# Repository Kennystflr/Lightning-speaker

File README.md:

# Lightning-speaker
Project of Kenny Saint Fleur, Mathys Minsac, Lavallee Alexandre, Florian Bonnet--Galand and Victor Morel. 1st Year ENSEA students.
Design of the electronic board for a speaker.
Using a STM32 microcontroller, audio codec and two class D amplifiers.

The purpose of this project is to design the electronic of a speaker. More specifically the goal is to take an entry signal from Jack 6.35 mm connector and to have sound coming out of a stereo loudspeaker. 
We could also have a parametric eq using 2 encoders 1 for the gain and 1 for the frequency we would be changing.
We also want to have the system working on battery with Usb-C power delivery to charge-up the battery and power up the system even if there is no battery connected.

There is a schematic of the projects detailed review on this repository's root. 

Basically, we would be calcultating coeficients for the SGTL5000 audio codec with the STM32 from the encoder's command. We can command up to 4 different filters with this method.
Then we would apply filters to the audio codec by sending the filter's coeficients through I2C communication protocol to the SGTL5000.
About the signal itself, it would enter into the audio codec, pass through the filters, be transmitted to the STM32 using I2S communication protocol and then would go through the Half Bridge Class D audio amplifer.
To charge up the battery, the 9V power supply (negociated with a source by the STM32) goes through a BMS who can bypass the battery in case it is dead or missing.

An issue we have met doing this was that the Half bridge was commuting between a positive voltage and ground which was a bad for the loudspeakears as the load. To resolve that we had to cut the rms continuous voltage 
using a genuinely calculated capacity.

As IC references we have :
-Microprocessor : STM32G491CET6
-Audio codec :SGTL5000XNLA3
-Battery Management System : BQ25306RTET
- USB-C protection IC : TCPP01-M12
- USB protection IC : USBLC6-2SC6
- Mosfet driver : UCC27325DR
- LDO 5V : AZ1117-5.0
- LDO 3.3V : BU33SD5WG-TR
- LDO 1.8V : BU18SD5WG-TRe

Unfortunately, the project wouldn't work in the end and we weren't able to debug it before the due time.
So we came up with a lifeboat plan of showing off our secondary board :

Project Specifications for the Replacement Project (aims to test the different codes made during the project and the PCB secondary board):

To test the LEDs, the potentiometer, and the encoder button, the LEDs are lit one by one, faster or slower depending on the value of the potentiometer.
The button on encoder 1 allows the LEDs to light up in the opposite direction.

To test the RGB (even though we only use 2 out of 3 LEDs) and the rotation of the encoder, the brightness of the red LED of encoder 2 is increased while the brightness of the blue LED is decreased when encoder 1 is rotated in one direction and vice versa when rotated in the other direction.

As a bonus, pressing the button on encoder 1 toggles the green LED of encoder 1 on or off.

*There is an demonstration video on the repository's root* : 

To push the project further we could have :
- had a bluetooth connection with a phone app to control the features.
- used the USB-C port's FS USB connected to the STM32 to have had sound going into the loudspeaker from an extern device as a computer or even a smartphone...

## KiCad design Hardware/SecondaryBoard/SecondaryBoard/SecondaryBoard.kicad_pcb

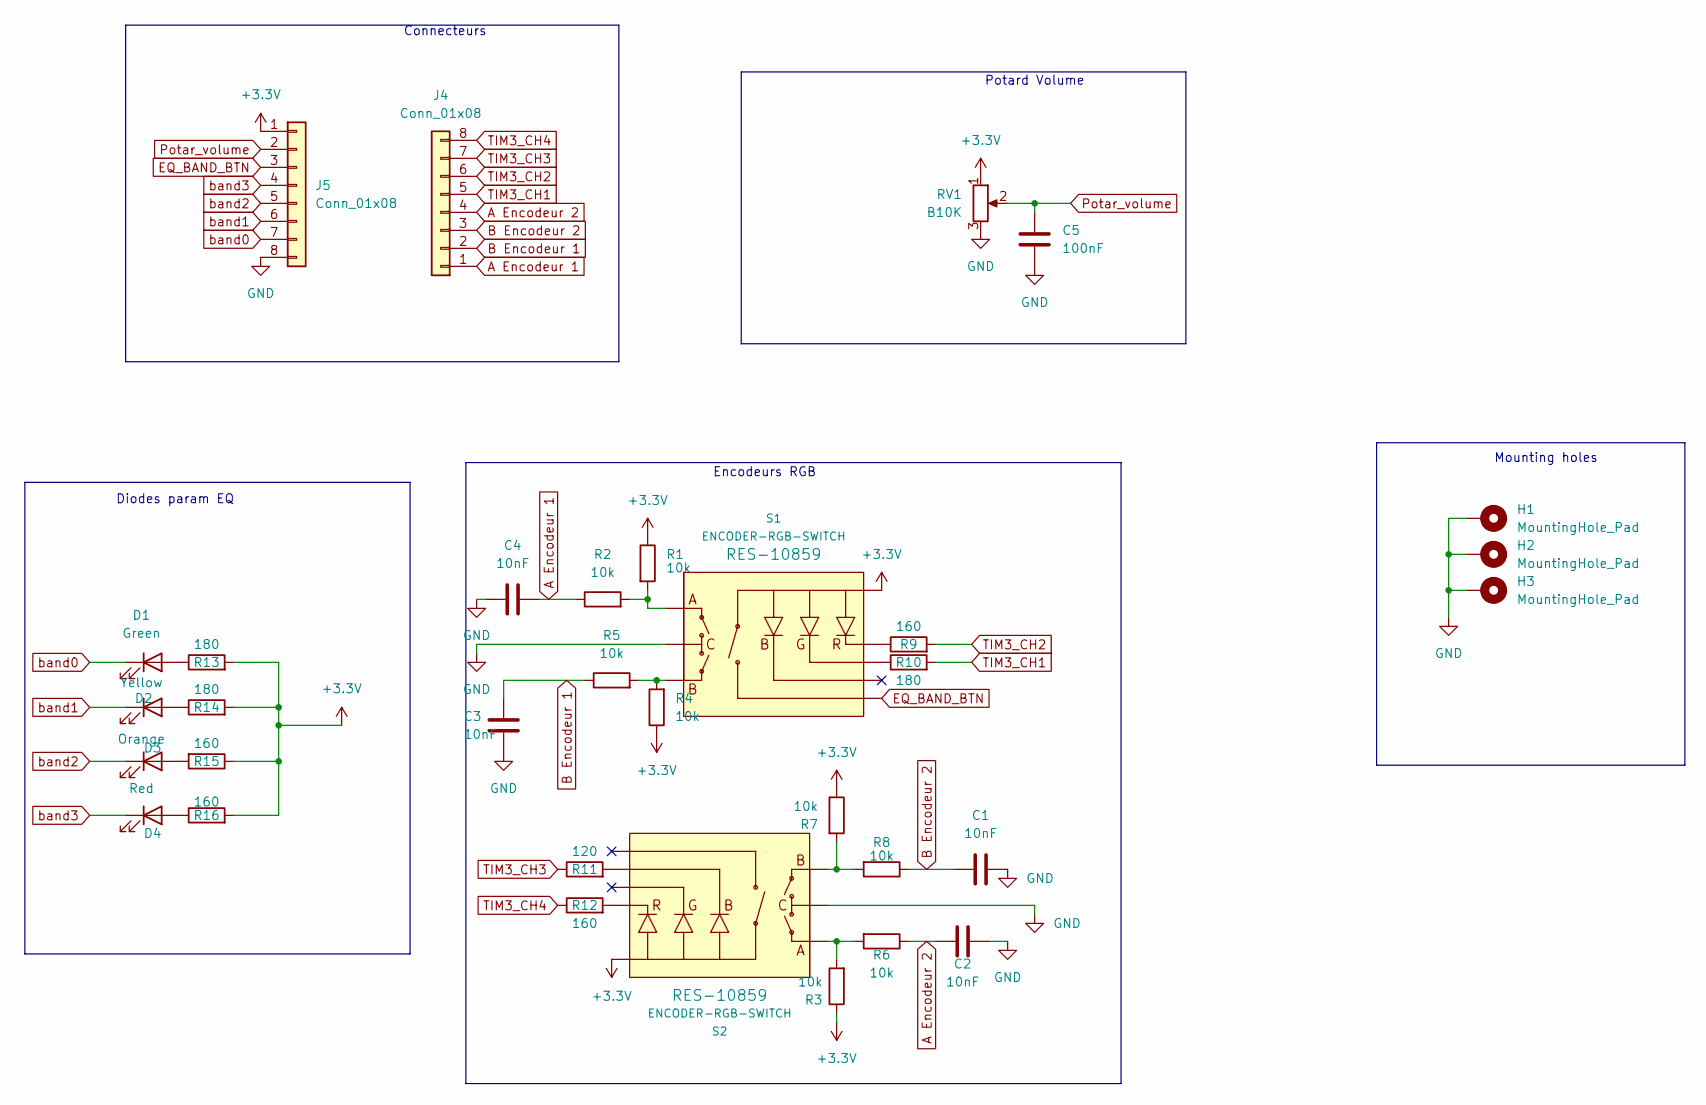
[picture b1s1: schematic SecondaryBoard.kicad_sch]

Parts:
C1, C2, C3, C4: 10nF; C_0603_1608Metric_Pad1.08x0.95mm_HandSolder
C5: 100nF; C_0603_1608Metric_Pad1.08x0.95mm_HandSolder
D1: Green; LED_D3.0mm
D2: Yellow; LED_D5.0mm
D3: Orange; LED_D5.0mm
D4: Red; LED_D5.0mm
H1, H2, H3: MountingHole_Pad; MountingHole_3.2mm_M3_DIN965_Pad
J4, J5: Conn_01x08; JST_XH_B8B-XH-AM_1x08_P2.50mm_Vertical
R1, R2, R3, R4, R5, R6, R7, R8: 10k; R_0603_1608Metric_Pad0.98x0.95mm_HandSolder
R9, R12, R15, R16: 160; R_0603_1608Metric_Pad0.98x0.95mm_HandSolder
R10, R13, R14: 180; R_0603_1608Metric_Pad0.98x0.95mm_HandSolder
R11: 120; R_0603_1608Metric_Pad0.98x0.95mm_HandSolder
RV1: B10K; Potentiometer_Alpha_RD901F-40-00D_Single_Vertical
S1, S2: ENCODER-RGB-SWITCH; ENCODER_LED_3

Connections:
+3.3V: J5.1, R1.1, R3.1, R4.1, R7.1, R13.2, R14.2, R15.1, R16.2, RV1.1, S1.5, S2.5
A Encodeur 1: C4.2, J4.1, R2.1
A Encodeur 2: C2.2, J4.4, R6.1
B Encodeur 1: C3.2, J4.2, R5.1
B Encodeur 2: C1.2, J4.3, R8.1
EQ_BAND_BTN: J5.3, S1.3
GND: C1.1, C2.1, C3.1, C4.1, C5.1, H1.1, H2.1, H3.1, J5.8, RV1.3, S1.C, S2.C
unnamed: D1.2 (A), R13.1
unnamed: D2.2 (A), R14.1
unnamed: D3.2 (A), R15.2
unnamed: D4.2 (A), R16.1
unnamed: R1.2, R2.2, S1.A
unnamed: R3.2, R6.2, S2.A
unnamed: R4.2, R5.2, S1.B
unnamed: R7.2, R8.2, S2.B
unnamed: R9.1, S1.1
unnamed: R10.1, S1.2
unnamed: R11.2, S2.4
unnamed: R12.2, S2.1
Potar_volume: C5.2, J5.2, RV1.2
TIM3_CH1: J4.5, R10.2
TIM3_CH2: J4.6, R9.2
TIM3_CH3: J4.7, R11.1
TIM3_CH4: J4.8, R12.1
band0: D1.1 (K), J5.7
band1: D2.1 (K), J5.6
band2: D3.1 (K), J5.5
band3: D4.1 (K), J5.4

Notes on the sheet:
Connecteurs
Encodeurs RGB
Diodes param EQ
Potard Volume
Mounting holes

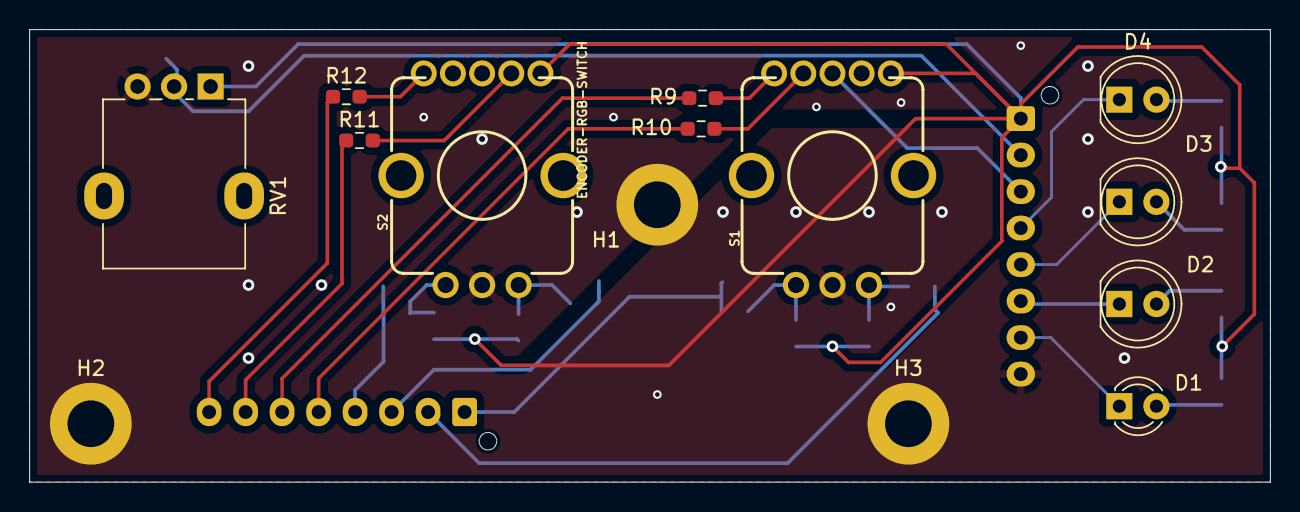
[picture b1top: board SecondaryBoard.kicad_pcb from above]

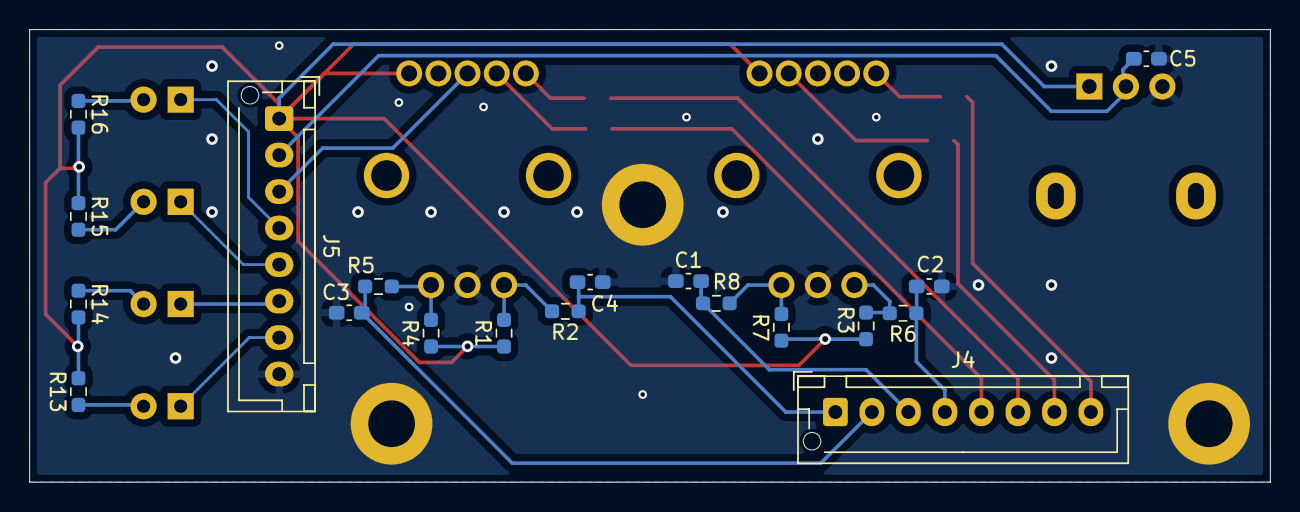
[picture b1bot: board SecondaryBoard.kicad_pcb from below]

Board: 2 copper layers, 85.0 x 31.0 mm, 33 parts (19 on the bottom side), 28 nets.

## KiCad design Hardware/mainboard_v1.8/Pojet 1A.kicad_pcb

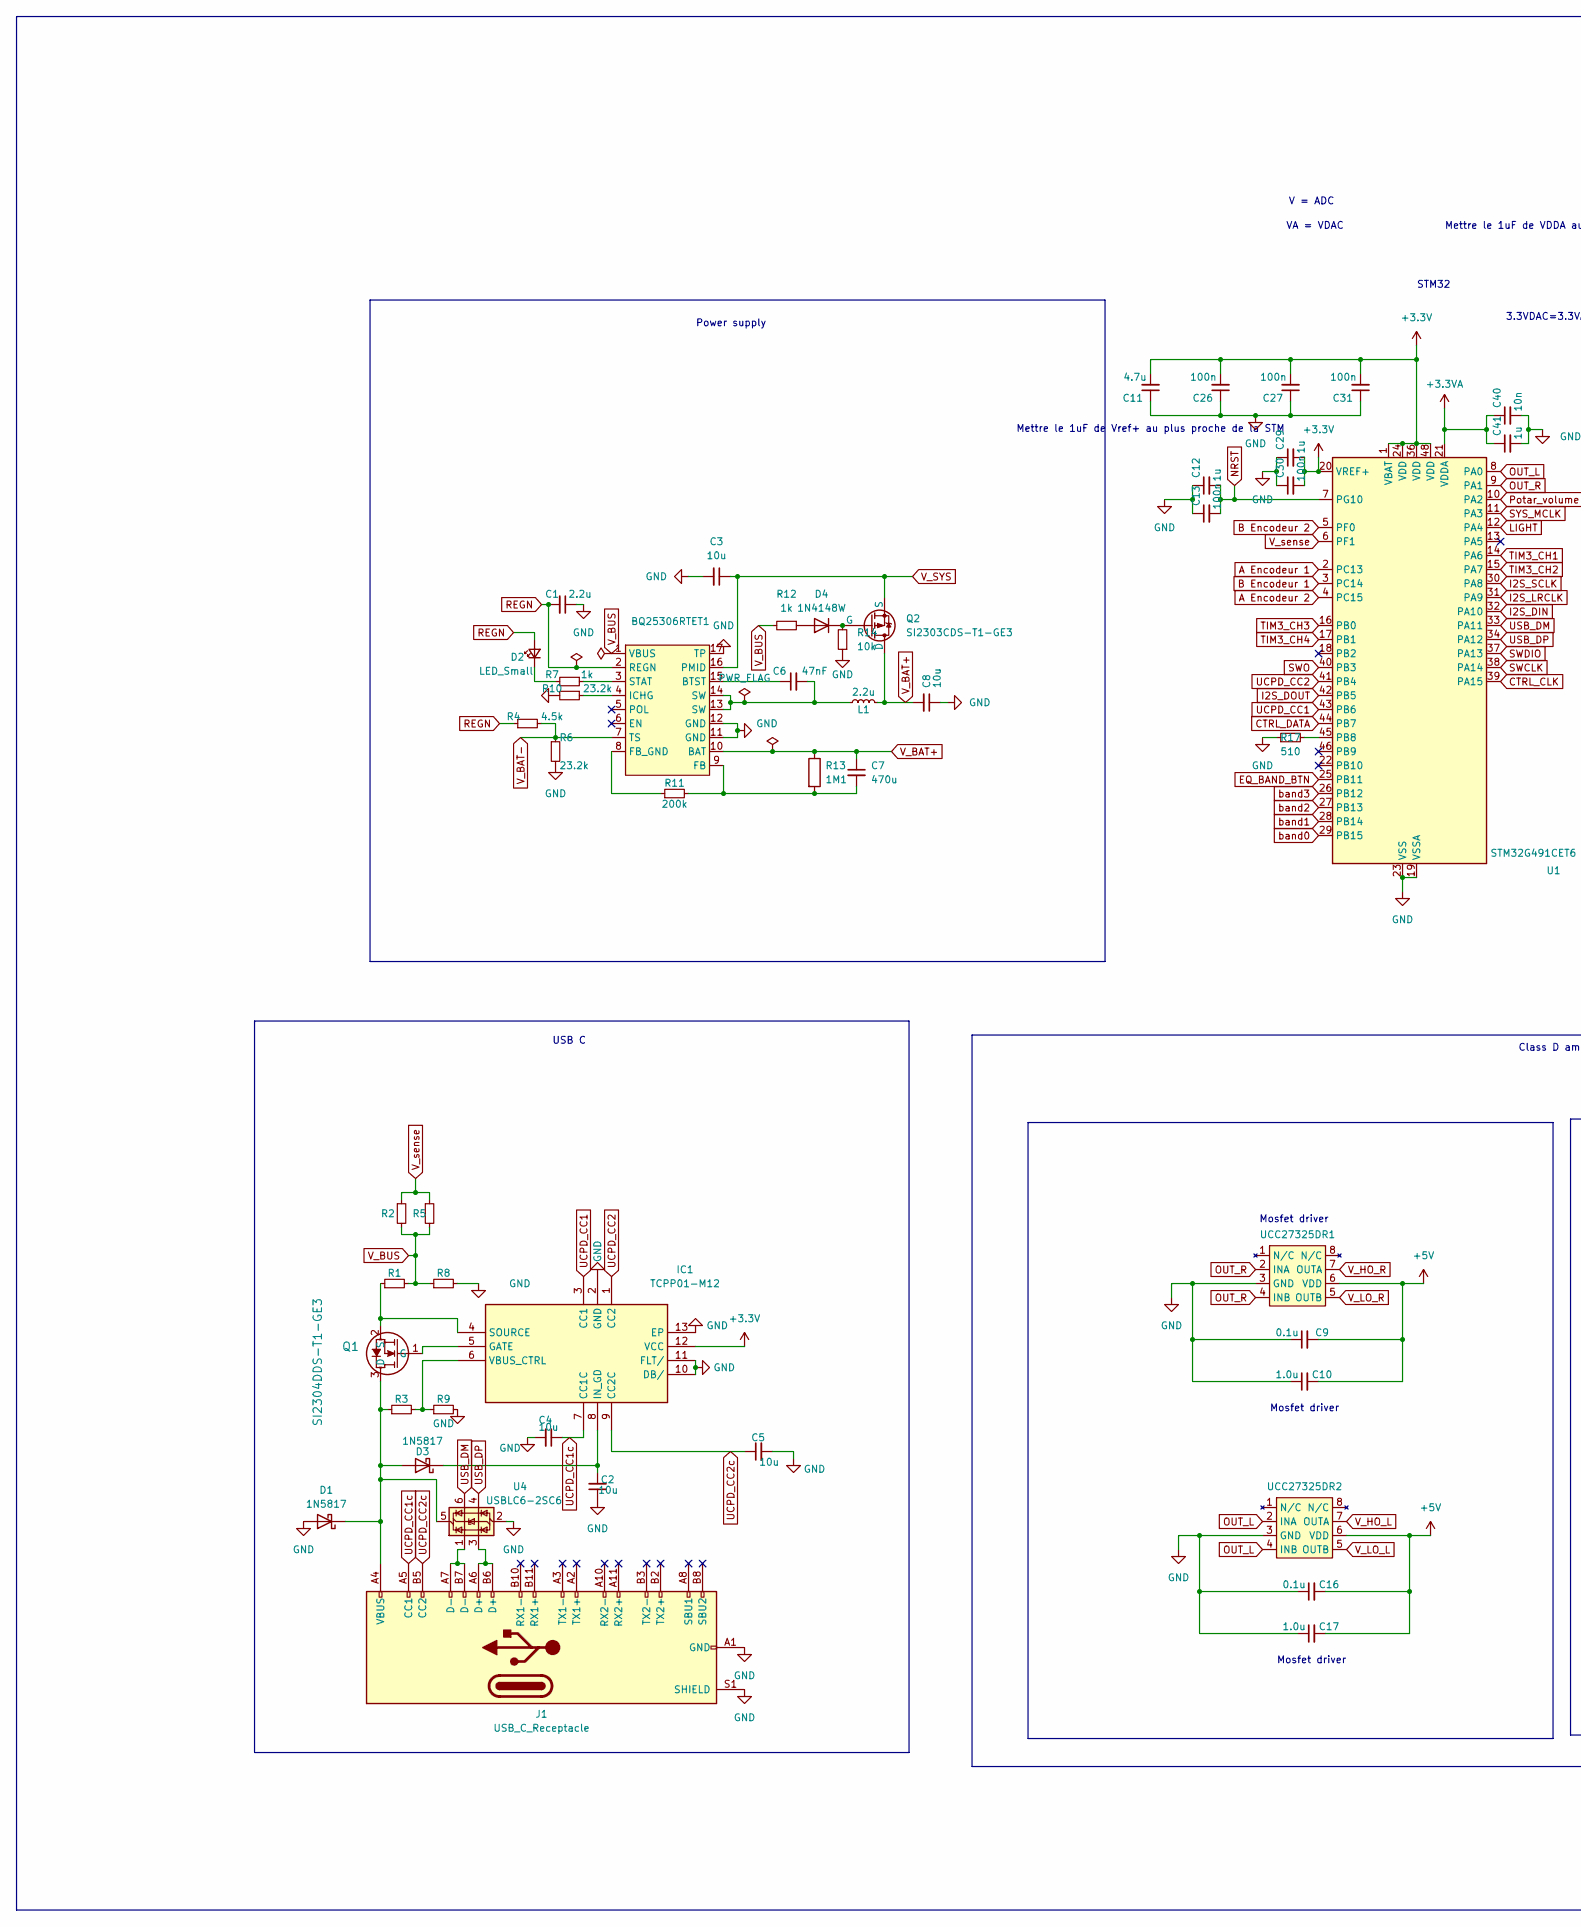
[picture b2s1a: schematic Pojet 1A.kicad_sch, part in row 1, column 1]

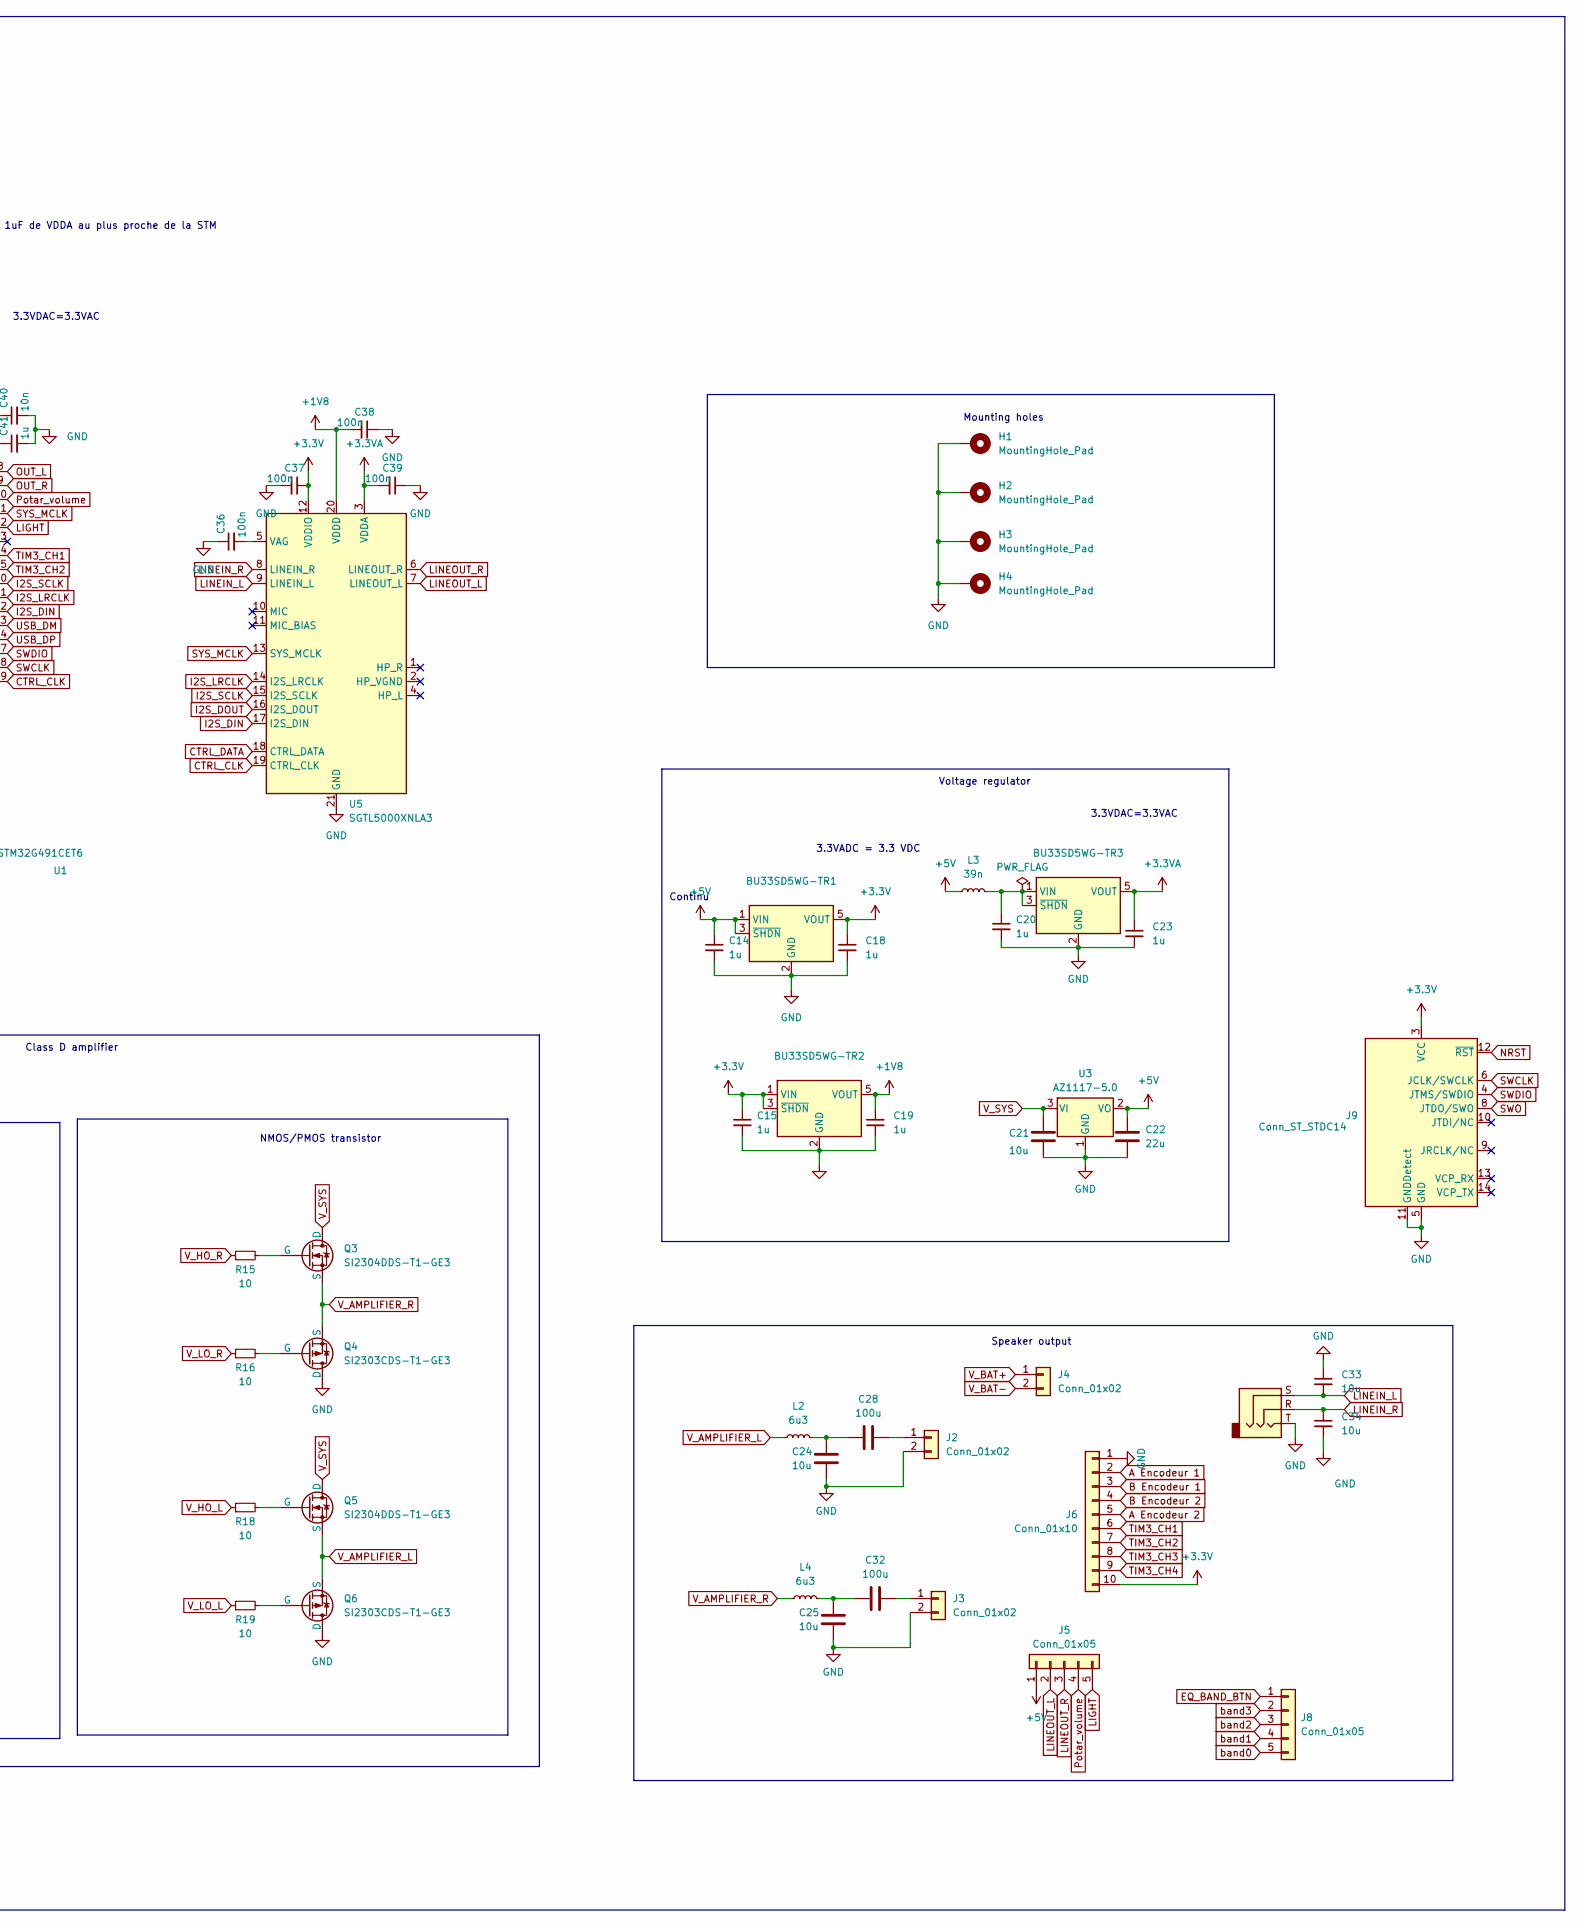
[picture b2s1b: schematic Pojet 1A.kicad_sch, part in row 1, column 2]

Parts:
BQ25306RTET1: WQFN-16-1EP_3x3mm_P0.5mm_EP1.75x1.75mm
BU33SD5WG-TR1, BU33SD5WG-TR2, BU33SD5WG-TR3: LM1117DT-3.3; SOT-23-5
C1: 2.2u; C_0603_1608Metric_Pad1.08x0.95mm_HandSolder
C2, C3, C4, C5, C8, C24, C25, C33, C34: 10u; C_0402_1005Metric_Pad0.74x0.62mm_HandSolder
C6: 47nF; C_0603_1608Metric_Pad1.08x0.95mm_HandSolder
C7: 470u; C_0603_1608Metric_Pad1.08x0.95mm_HandSolder
C9, C16: 0.1u; C_0603_1608Metric_Pad1.08x0.95mm_HandSolder
C10, C17: 1.0u; C_0603_1608Metric_Pad1.08x0.95mm_HandSolder
C11: 4.7u; C_0603_1608Metric_Pad1.08x0.95mm_HandSolder
C12, C14, C15, C18, C19, C20, C23, C29, C41: 1u; C_0603_1608Metric_Pad1.08x0.95mm_HandSolder
C13, C26, C27, C30, C31, C36, C37, C38, C39: 100n; C_0402_1005Metric_Pad0.74x0.62mm_HandSolder
C21: 10u; C_0603_1608Metric_Pad1.08x0.95mm_HandSolder
C22: 22u; C_0805_2012Metric_Pad1.18x1.45mm_HandSolder
C28, C32: 100u; C_Radial_D5.0mm_H11.0mm_P2.00mm
C40: 10n; C_0402_1005Metric_Pad0.74x0.62mm_HandSolder
D1, D3: 1N5817; D_DO-41_SOD81_P10.16mm_Horizontal
D2: LED_Small; LED_D10.0mm
D4: 1N4148W; D_SOD-123
H1, H2, H3, H4: MountingHole_Pad; MountingHole_3.2mm_M3_DIN965_Pad
IC1: TCPP01-M12; LQFN-12-1EP_2x2mm_P0.5mm_EP0.7x0.7mm; Manufacturer_Part_Number TCPP01-M12; Mouser Part Number 511-TCPP01-M12
J1: USB_C_Receptacle; USB_C_Receptacle_GCT_USB4115-03-C
J2, J3, J4: Conn_01x02; JST_XH_B2B-XH-A_1x02_P2.50mm_Vertical
J5, J8: Conn_01x05; PinHeader_1x05_P2.54mm_Vertical
J6: Conn_01x10; PinHeader_1x10_P2.54mm_Vertical
J7: AudioJack3; Jack_6.35mm_Neutrik_NJ3FD-V_Vertical
J9: Conn_ST_STDC14; PinHeader_2x07_P1.27mm_Vertical_SMD
L1: 2.2u; L_0603_1608Metric_Pad1.05x0.95mm_HandSolder
L2, L4: 6u3; L_Vishay_IFSC-1515AH_4x4x1.8mm
L3: 39n; L_0603_1608Metric_Pad1.05x0.95mm_HandSolder
Q1, Q3, Q5: SI2304DDS-T1-GE3; SOT-23
Q2, Q4, Q6: SI2303CDS-T1-GE3; SOT-23
R1, R2, R3, R5, R8, R9: R_0603_1608Metric_Pad0.98x0.95mm_HandSolder
R4: 4.5k; R_0603_1608Metric_Pad0.98x0.95mm_HandSolder
R6, R10: 23.2k; R_0603_1608Metric_Pad0.98x0.95mm_HandSolder
R7, R12: 1k; R_0603_1608Metric_Pad0.98x0.95mm_HandSolder
R11: 200k; R_0603_1608Metric_Pad0.98x0.95mm_HandSolder
R13: 1M1; R_0603_1608Metric_Pad0.98x0.95mm_HandSolder
R14: 10k; R_0603_1608Metric_Pad0.98x0.95mm_HandSolder
R15, R16, R18, R19: 10; R_0603_1608Metric_Pad0.98x0.95mm_HandSolder
R17: 510; R_0603_1608Metric_Pad0.98x0.95mm_HandSolder
U1: STM32G491CET6; LQFP-48_7x7mm_P0.5mm
U3: AZ1117-5.0; SOT-223-3_TabPin2
U4: USBLC6-2SC6; SOT-23-6
U5: SGTL5000XNLA3; QFN-20-1EP_3x3mm_P0.4mm_EP1.65x1.65mm
UCC27325DR1, UCC27325DR2: SOIC-8_3.9x4.9mm_P1.27mm

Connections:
+1V8: BU33SD5WG-TR2.5 (VOUT), C19.1, C38.2, U5.20 (VDDD)
+3.3V: BU33SD5WG-TR1.5 (VOUT), BU33SD5WG-TR2.1 (VIN), BU33SD5WG-TR2.3 (~SHDN), C11.2, C15.1, C18.1, C26.2, C27.2, C29.2, C30.2, C31.2, C37.1, IC1.12 (VCC), J6.10, J9.3 (VCC), U1.1 (VBAT), U1.20 (VREF+), U1.24 (VDD), U1.36 (VDD), U1.48 (VDD), U5.12 (VDDIO)
+3.3VA: BU33SD5WG-TR3.5 (VOUT), C23.1, C39.2, C40.1, C41.1, U1.21 (VDDA), U5.3 (VDDA)
+5V: BU33SD5WG-TR1.1 (VIN), BU33SD5WG-TR1.3 (~SHDN), C9.2, C10.2, C14.1, C16.2, C17.2, C22.1, J5.1, L3.1, U3.2 (VO), UCC27325DR1.6 (VDD), UCC27325DR2.6 (VDD)
A Encodeur 1: J6.2, U1.2 (PC13)
A Encodeur 2: J6.5, U1.4 (PC15)
B Encodeur 1: J6.3, U1.3 (PC14)
B Encodeur 2: J6.4, U1.5 (PF0)
CTRL_CLK: U1.39 (PA15), U5.19 (CTRL_CLK)
CTRL_DATA: U1.44 (PB7), U5.18 (CTRL_DATA)
EQ_BAND_BTN: J8.1, U1.25 (PB11)
GND: BQ25306RTET1.11 (GND), BQ25306RTET1.12 (GND), BQ25306RTET1.17 (TP), BU33SD5WG-TR1.2 (GND), BU33SD5WG-TR2.2 (GND), BU33SD5WG-TR3.2 (GND), C1.1, C2.1, C3.2, C4.2, C5.2, C8.1, C9.1, C10.1, C11.1, C12.1, C13.1, C14.2, C15.2, C16.1, C17.1, C18.2, C19.2, C20.2, C21.2, C22.2, C23.2, C24.2, C25.2, C26.1, C27.1, C29.1, C30.1, C31.1, C33.1, C34.2, C36.1, C37.2, C38.1, C39.1, C40.2, C41.2, D1.2 (A), H1.1, H2.1, H3.1, H4.1, IC1.2 (GND), IC1.10 (DB/), IC1.11 (FLT/), IC1.13 (EP), J1.A1 (GND), J1.A12 (GND), J1.B1 (GND), J1.B12 (GND), J1.S1 (SHIELD), J2.2, J3.2, J6.1, J7.T, J9.5 (GND), J9.7 (GND), J9.11 (GNDDetect), Q4.1 (D), Q6.1 (D), R6.2, R8.2, R9.2, R10.2, R14.1, R17.1, U1.19 (VSSA), U1.23 (VSS), U1.35 (VSS), U1.47 (VSS), U3.1 (GND), U4.2 (GND), U5.21 (GND), UCC27325DR1.3 (GND), UCC27325DR2.3 (GND)
I2S_DIN: U1.32 (PA10), U5.17 (I2S_DIN)
I2S_DOUT: U1.42 (PB5), U5.16 (I2S_DOUT)
I2S_LRCLK: U1.31 (PA9), U5.14 (I2S_LRCLK)
I2S_SCLK: U1.30 (PA8), U5.15 (I2S_SCLK)
LIGHT: J5.5, U1.12 (PA4)
LINEIN_L: C33.2, J7.S, U5.9 (LINEIN_L)
LINEIN_R: C34.1, J7.R, U5.8 (LINEIN_R)
LINEOUT_L: J5.2, U5.7 (LINEOUT_L)
LINEOUT_R: J5.3, U5.6 (LINEOUT_R)
NRST: C12.2, C13.2, J9.12 (~RST), U1.7 (PG10)
unnamed: BQ25306RTET1.15 (BTST), C6.1
unnamed: BQ25306RTET1.9 (FB), C7.2, R11.2, R13.2
unnamed: BQ25306RTET1.8 (FB_GND), R11.1
unnamed: BQ25306RTET1.4 (ICHG), R10.1
unnamed: BQ25306RTET1.3 (STAT), R7.1
unnamed: BQ25306RTET1.13 (SW), BQ25306RTET1.14 (SW), C6.2, L1.1
unnamed: BU33SD5WG-TR3.1 (VIN), BU33SD5WG-TR3.3 (~SHDN), C20.1, L3.2
unnamed: C24.1, C28.1, L2.2
unnamed: C25.1, C32.1, L4.2
unnamed: D1.1 (K), D3.2 (A), J1.A4 (VBUS), J1.A9 (VBUS), J1.B4 (VBUS), J1.B9 (VBUS), Q1.3 (D), R3.1, U4.5 (VBUS)
unnamed: D2.1 (K), R7.2
unnamed: C2.2, D3.1 (K), IC1.8 (IN_GD)
unnamed: D4.2 (A), R12.1
unnamed: D4.1 (K), Q2.2 (G), R14.2
unnamed: IC1.5 (GATE), Q1.1 (G)
unnamed: IC1.4 (SOURCE), Q1.2 (S), R1.1
unnamed: IC1.6 (VBUS_CTRL), R3.2, R9.1
unnamed: J1.A6 (D+), J1.B6 (D+), U4.3 (I/O2)
unnamed: J1.A7 (D-), J1.B7 (D-), U4.1 (I/O1)
unnamed: C28.2, J2.1
unnamed: C32.2, J3.1
unnamed: Q3.2 (G), R15.2
unnamed: Q4.2 (G), R16.2
unnamed: Q5.2 (G), R18.2
unnamed: Q6.2 (G), R19.2
unnamed: R17.2, U1.45 (PB8)
unnamed: C36.2, U5.5 (VAG)
OUT_L: U1.8 (PA0), UCC27325DR2.2 (INA), UCC27325DR2.4 (INB)
OUT_R: U1.9 (PA1), UCC27325DR1.2 (INA), UCC27325DR1.4 (INB)
Potar_volume: J5.4, U1.10 (PA2)
REGN: BQ25306RTET1.2 (REGN), C1.2, D2.2 (A), R4.1
SWCLK: J9.6 (JCLK/SWCLK), U1.38 (PA14)
SWDIO: J9.4 (JTMS/SWDIO), U1.37 (PA13)
SWO: J9.8 (JTDO/SWO), U1.40 (PB3)
SYS_MCLK: U1.11 (PA3), U5.13 (SYS_MCLK)
TIM3_CH1: J6.6, U1.14 (PA6)
TIM3_CH2: J6.7, U1.15 (PA7)
TIM3_CH3: J6.8, U1.16 (PB0)
TIM3_CH4: J6.9, U1.17 (PB1)
UCPD_CC1: IC1.3 (CC1), U1.43 (PB6)
UCPD_CC1c: C4.1, IC1.7 (CC1C), J1.A5 (CC1)
UCPD_CC2: IC1.1 (CC2), U1.41 (PB4)
UCPD_CC2c: C5.1, IC1.9 (CC2C), J1.B5 (CC2)
USB_DM: U1.33 (PA11), U4.6 (I/O1)
USB_DP: U1.34 (PA12), U4.4 (I/O2)
V_AMPLIFIER_L: L2.1, Q5.3 (S), Q6.3 (S)
V_AMPLIFIER_R: L4.1, Q3.3 (S), Q4.3 (S)
V_BAT+: BQ25306RTET1.10 (BAT), C7.1, C8.2, J4.1, L1.2, Q2.1 (D), R13.1
V_BAT-: BQ25306RTET1.7 (TS), J4.2, R4.2, R6.1
V_BUS: BQ25306RTET1.1 (VBUS), R1.2, R2.2, R5.2, R8.1, R12.2
V_HO_L: R18.1, UCC27325DR2.7 (OUTA)
V_HO_R: R15.1, UCC27325DR1.7 (OUTA)
V_LO_L: R19.1, UCC27325DR2.5 (OUTB)
V_LO_R: R16.1, UCC27325DR1.5 (OUTB)
V_SYS: BQ25306RTET1.16 (PMID), C3.1, C21.1, Q2.3 (S), Q3.1 (D), Q5.1 (D), U3.3 (VI)
V_sense: R2.1, R5.1, U1.6 (PF1)
band0: J8.5, U1.29 (PB15)
band1: J8.4, U1.28 (PB14)
band2: J8.3, U1.27 (PB13)
band3: J8.2, U1.26 (PB12)

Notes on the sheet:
Class D amplifier
V = ADC
Power supply
Mounting holes
Mettre le 1uF de VDDA au plus proche de la STM
Voltage regulator
Mosfet driver
USB C
3.3VDAC=3.3VAC
VA = VDAC
Mettre le 1uF de Vref+ au plus proche de la STM
NMOS/PMOS transistor
Speaker output
STM32
3.3VADC = 3.3 VDC
Continu

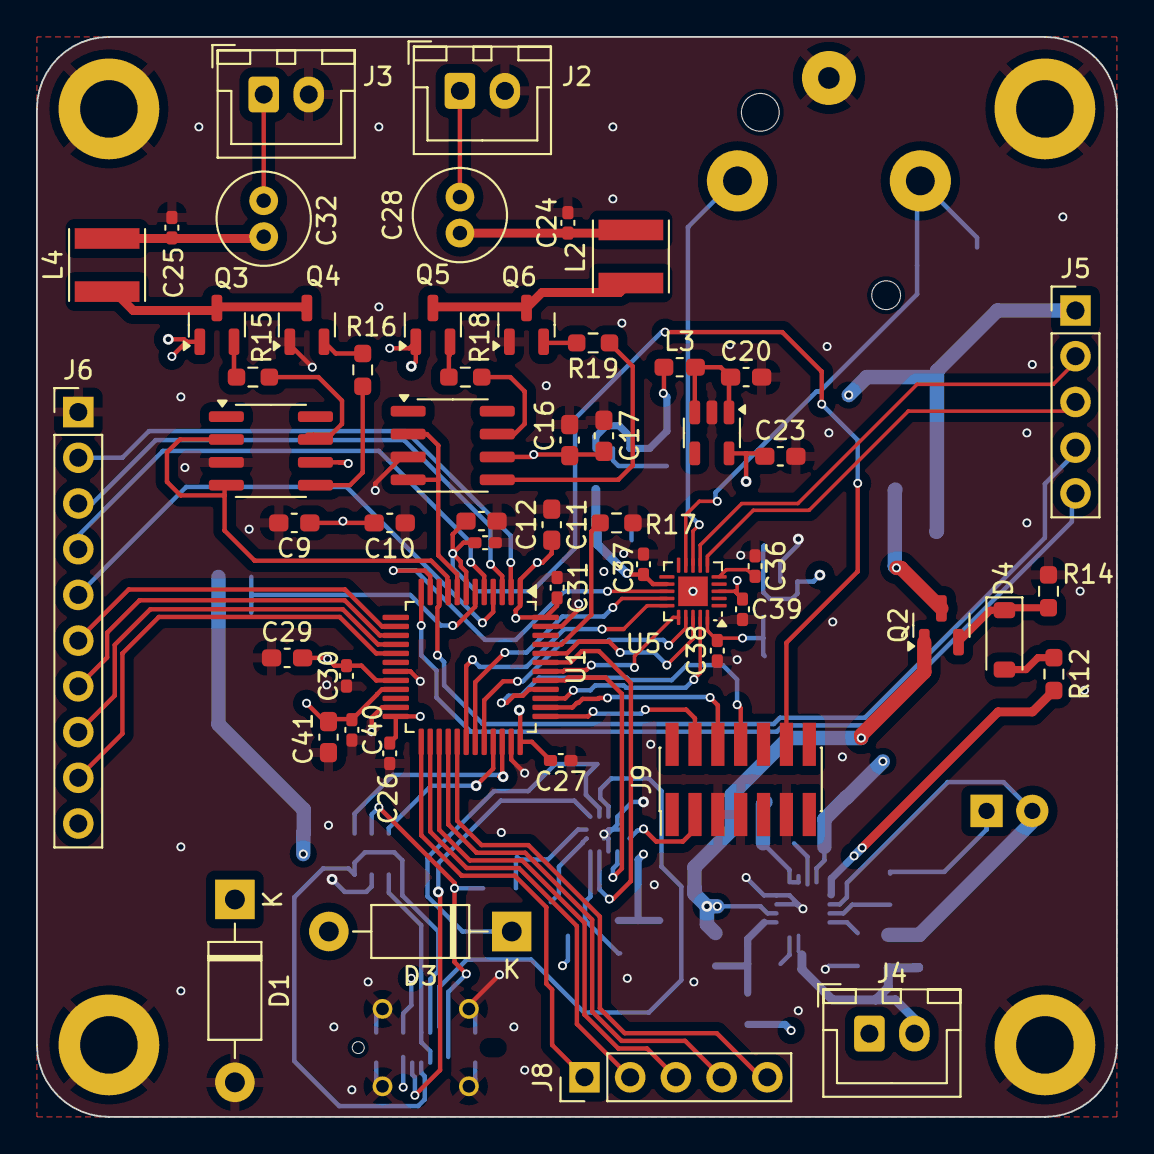
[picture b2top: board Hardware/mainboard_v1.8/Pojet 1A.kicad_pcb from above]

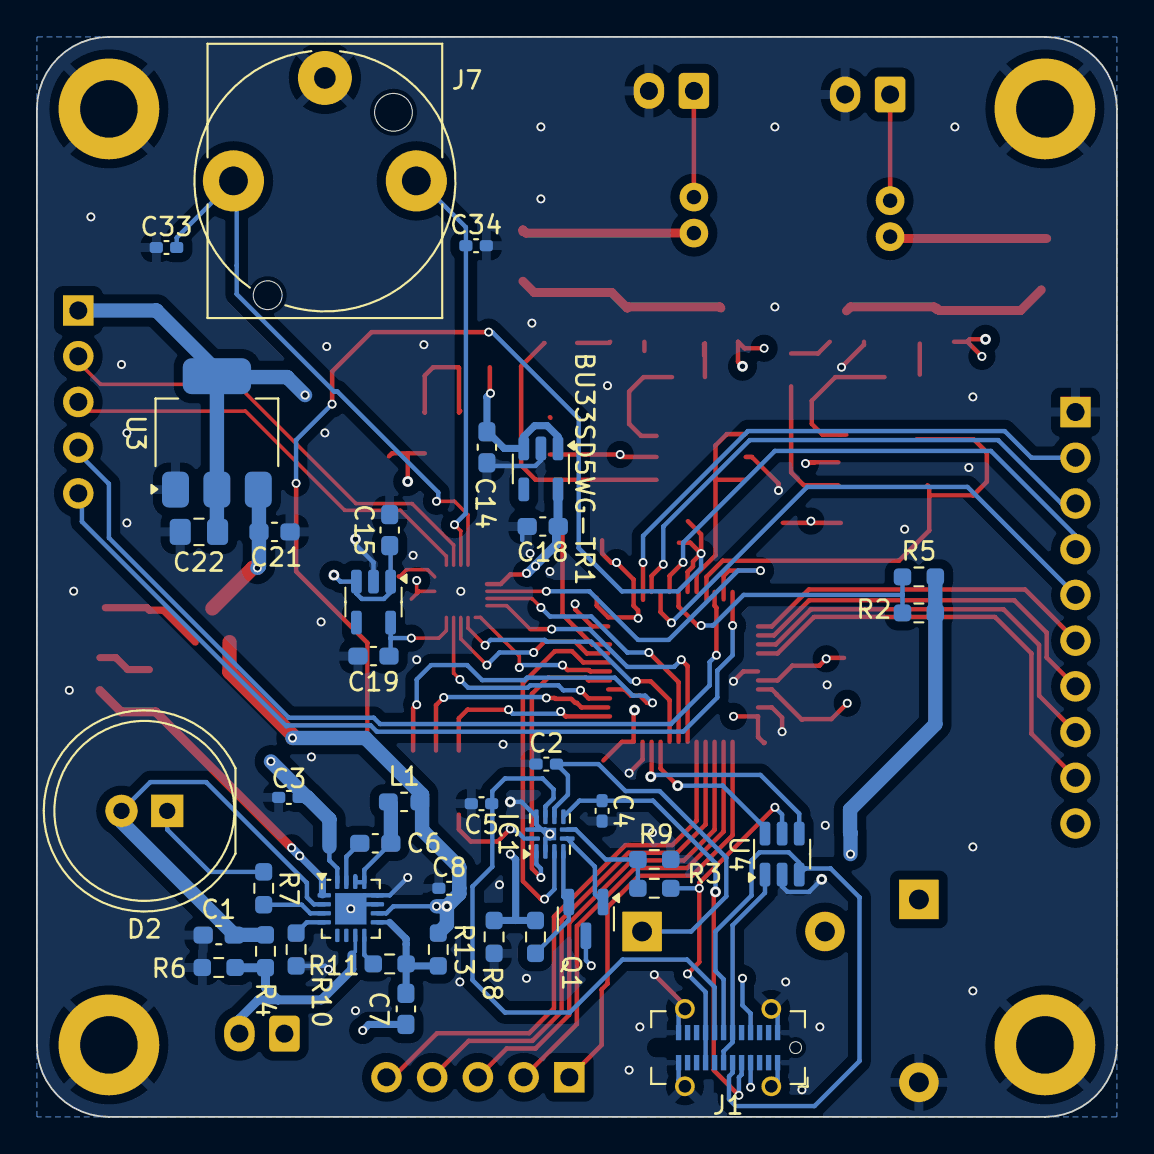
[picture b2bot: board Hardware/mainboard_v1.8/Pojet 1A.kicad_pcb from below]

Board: 4 copper layers, 60.0 x 60.0 mm, 97 parts (39 on the bottom side), 82 nets.

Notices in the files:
Software/Pojetremplacant1A/Core/Src/stm32g4xx_hal_msp.c:
Copyright (c) 2024 STMicroelectronics.
All rights reserved.
This software is licensed under terms that can be found in the LICENSE file
